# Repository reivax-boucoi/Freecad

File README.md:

### Freecad project repo
Here you'll find misc. 3D modeling projects ranging from home improvement to electronics tinkering.

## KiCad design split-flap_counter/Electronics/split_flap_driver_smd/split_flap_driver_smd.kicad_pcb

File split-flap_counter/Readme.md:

# Split flap counter project

This project started as a joke, to display the "number of consecutive days without incident", as we were blowing up chips regularly in the lab.

The counter consists of 2 digit wheels capable of displaying the numbers 00 through 99. (Given the frequency of incidents, a 3rd wheel wasn't considered).
Each day, the counter increments by 1. When a "happy little accident" occurs, simply insert a chip into the bin to cause the counter to reset in a satisfying motion.

This project was developped in a couple days, mixing 3D printing, electronics and minimal code.

## Hardware

### Mechanicals

The hardware was designed using Freecad 0.9 for the mechanical part. 
It uses multimaterial printing for the digit flaps, and regular PLA prints for the rest. The 2 wheels consist of mirrored parts facing each other, the assembly providing overall support of the drums.
The base structure was inspired by [Thomas H 3D](https://www.printables.com/model/69603-split-flap-counter-fully-printable) project, his being a single digit purely manual version. The flaps were customized for multi-material printing by [0Celta](https://www.printables.com/model/133058-multi-material-flaps-for-split-flap-counter).  

A ready made printable of the structure can be found [here](/Mechanical/3mF_exports_toPrint/full_plate.3mF).  
The individual printable parts are located in [/Mechanical/3mF_exports_toPrint/](/Mechanical/3mF_exports_toPrint/):
- 2x **Drum**
- 2x **Drum_end**
- 2x **Frame** (1 normal, 1 mirrored)
- 1x **JointKey**
- 1x **JointShaft**
- 2x **Flaps** (sets of 5 dual sided flaps)  

Additionnal hardware required:
- 2x **28-BYJ-48** 5V stepper motors
- 4x **M2x10** screws for the limit switches
- 4x **M3x8** screws for the motor mount
- 2x limit switches: mine were salvaged from an old industrial grade printer, I don't have the reference, they are similar-ish to Alps SSCTL10400.  

2 ventilation valve stepper motors are used, which are dirt cheap and run of 5V directly. They have a resolution of approx. 2048 steps per turn (in full step mode, not exact !) which is plenty for our application. One drawback is that they are quite slow: I found 5RPM to be a reliable value, i.e. ~12s to complete a revolution. Sliding lever microswitches provide zeroing on each wheel.  

### Assembly

### Electronics

Kicad 8.0 was used for the electronics (schematic and placement), although the circuit was manually assembled using dead-bug technique later on, because of it's simplicity. Nonetheless, a [schematic](/split-flap_counter/Electronics/split_flap_driver/schematic.pdf) and example [layout](/split-flap_counter/Electronics/split_flap_driver/) are available for reference.  

The project is powered by a 5V supply (>500mA required), which could be a generic USB wall charger.
The steppers are controlled using an ULN2003 Darlignton driver + an extra NPN since I required 8 channels for the 2x4 stepper coils. The buttons & limit switches inputs were filtered since the code is interrupt driven and without any debouncing. A hidden button allows manual incrementation for testing purposes.  

The 4MHz crystal oscillator frequency can be dialed-in using a trimmer cap to within tens of seconds per day of accuracy, which is sufficient for rough day keeping.

### Software

The software was developped in plain low level C and compiled using AVR-GCC and Avrdude (custom Makefile and [precompiled hex](/split-flap_counter/SW/main.hex) are provided). The MCU runs at 4MHz, and the program occupies 770 bytes of the 2kB of available program space.  

Fuse settings: `lfuse:w:0xfd:m -U hfuse:w:0xdf:m -U efuse:w:0xff:m`  

Resource allocation:
- TIMER0: triggers at ~400hz, used for stepper state machine and button debouncing.
- TIMER1: triggers every 8s, used for timekeeping (daily trigger)
- INT0: "zero" limit switch for the unit wheel. Configured as falling edge interrupt to reset position.
- INT1: "zero" limit switch for the tens wheel. Configured as falling edge interrupt to reset position.

The zeroing routine ensure a least half a turn of each wheel, even if the wheel was already diplaying a zero, for your enjoyment ☺.  
Upon zeroing, the time is also reset such that the display will increment 24 hours after the last reset.

To build the program use the `make` command, and use `make program` to upload it (be sure to specify your programmer in the Makefile *AVRDUDE_PROGRAMMER* field).

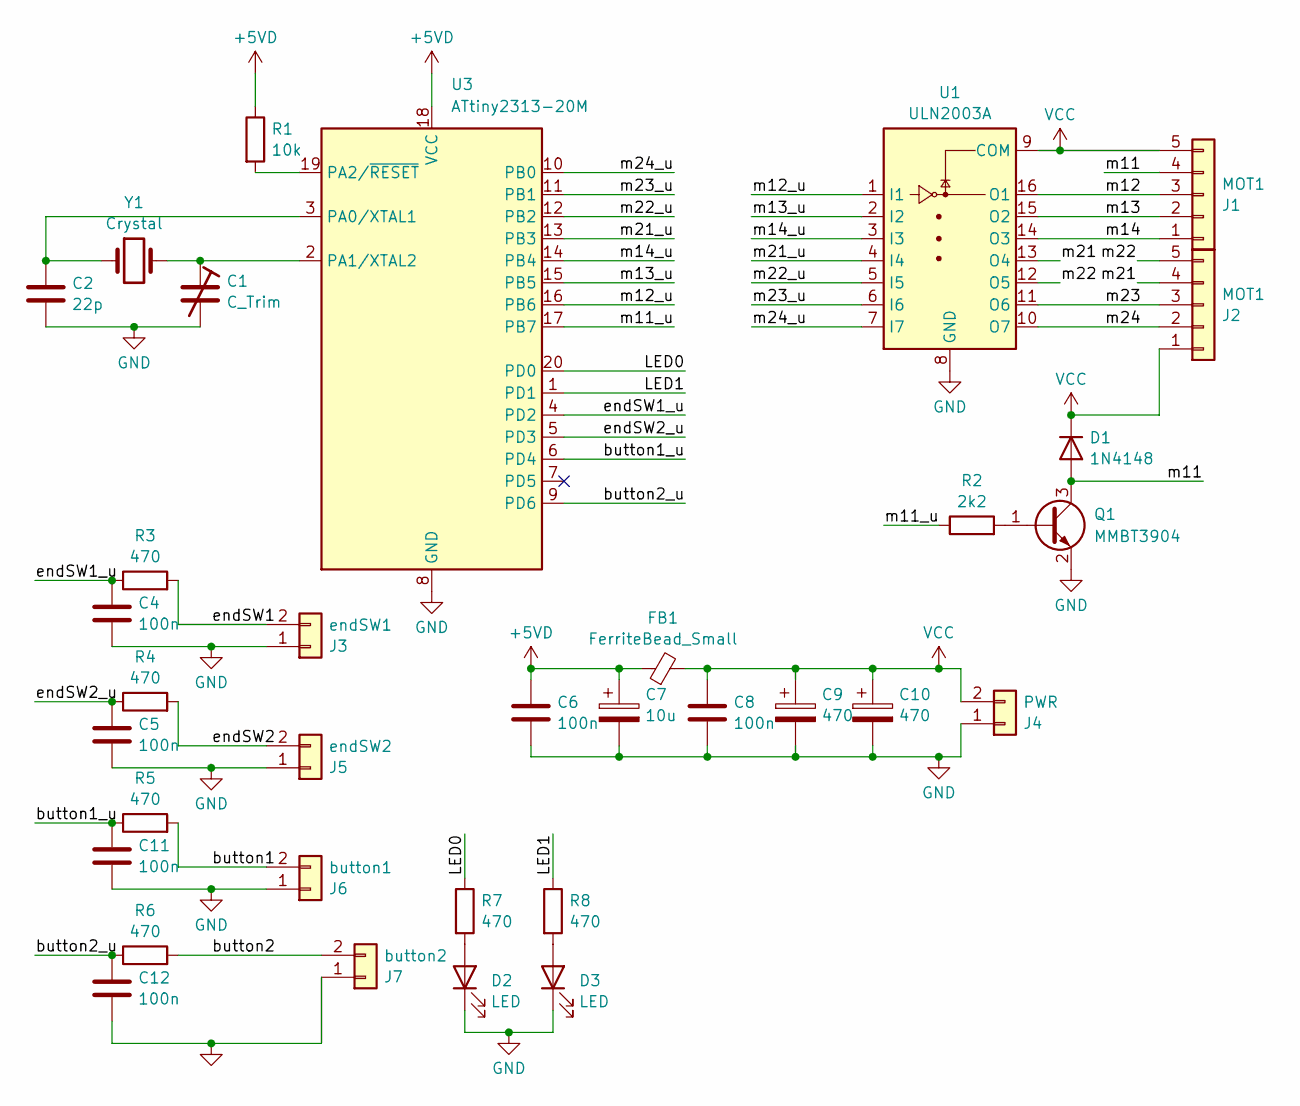
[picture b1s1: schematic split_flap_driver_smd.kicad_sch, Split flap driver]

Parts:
C1: C_Trim; Potentiometer_Bourns_3314J_Vertical
C2: 22p; C_0402_1005Metric
C4, C5, C6, C8, C11, C12: 100n; C_0402_1005Metric
C7: 10u; C_0805_2012Metric
C9, C10: 470; C_0805_2012Metric
D1: 1N4148; D_MicroMELF
D2, D3: LED; D_0603_1608Metric
FB1: FerriteBead_Small; L_0603_1608Metric
J1, J2: MOT1; JST_SH_SM05B-SRSS-TB_1x05-1MP_P1.00mm_Horizontal
J3: endSW1; JST_ZH_B2B-ZR_1x02_P1.50mm_Vertical
J4: PWR; JST_ZH_B2B-ZR_1x02_P1.50mm_Vertical
J5: endSW2; JST_ZH_B2B-ZR_1x02_P1.50mm_Vertical
J6: button1; JST_ZH_B2B-ZR_1x02_P1.50mm_Vertical
J7: button2; JST_ZH_B2B-ZR_1x02_P1.50mm_Vertical
Q1: MMBT3904; SOT-23
R1: 10k; R_0402_1005Metric
R2: 2k2; R_0402_1005Metric
R3, R4, R5, R6, R7, R8: 470; R_0402_1005Metric
U1: ULN2003A; TSSOP-16_4.4x5mm_P0.65mm
U3: ATtiny2313-20M; MLF-20-1EP_4x4mm_P0.5mm_EP2.6x2.6mm
Y1: Crystal; Crystal_SMD_2016-4Pin_2.0x1.6mm

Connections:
+5VD: C6.1, C7.1, FB1.1, R1.1, U3.18 (VCC)
/LED0: R7.1, U3.20 (PD0)
/LED1: R8.1, U3.1 (PD1)
/button1: J6.2, R5.2
/button1_u: C11.1, R5.1, U3.6 (PD4)
/button2: J7.2, R6.2
/button2_u: C12.1, R6.1, U3.9 (PD6)
/endSW1: J3.2, R3.2
/endSW1_u: C4.1, R3.1, U3.4 (PD2)
/endSW2: J5.2, R4.2
/endSW2_u: C5.1, R4.1, U3.5 (PD3)
/m11: D1.2 (A), J1.4, Q1.3 (C)
/m11_u: R2.1, U3.17 (PB7)
/m12: J1.3, U1.16 (O1)
/m12_u: U1.1 (I1), U3.16 (PB6)
/m13: J1.2, U1.15 (O2)
/m13_u: U1.2 (I2), U3.15 (PB5)
/m14: J1.1, U1.14 (O3)
/m14_u: U1.3 (I3), U3.14 (PB4)
/m21: J2.4, U1.13 (O4)
/m21_u: U1.4 (I4), U3.13 (PB3)
/m22: J2.5, U1.12 (O5)
/m22_u: U1.5 (I5), U3.12 (PB2)
/m23: J2.3, U1.11 (O6)
/m23_u: U1.6 (I6), U3.11 (PB1)
/m24: J2.2, U1.10 (O7)
/m24_u: U1.7 (I7), U3.10 (PB0)
GND: C1.2, C2.2, C4.2, C5.2, C6.2, C7.2, C8.2, C9.2, C10.2, C11.2, C12.2, D2.1 (K), D3.1 (K), J3.1, J4.1, J5.1, J6.1, J7.1, Q1.2 (E), U1.8 (GND), U3.8 (GND), U3.21 (GND)
unnamed: D2.2 (A), R7.2
unnamed: D3.2 (A), R8.2
unnamed: Q1.1 (B), R2.2
unnamed: C2.1, U3.3 (PA0/XTAL1), Y1.1
unnamed: C1.1, U3.2 (PA1/XTAL2), Y1.2
unnamed: R1.2, U3.19 (PA2/~RESET)
VCC: C8.1, C9.1, C10.1, D1.1 (K), FB1.2, J1.5, J2.1, J4.2, U1.9 (COM)

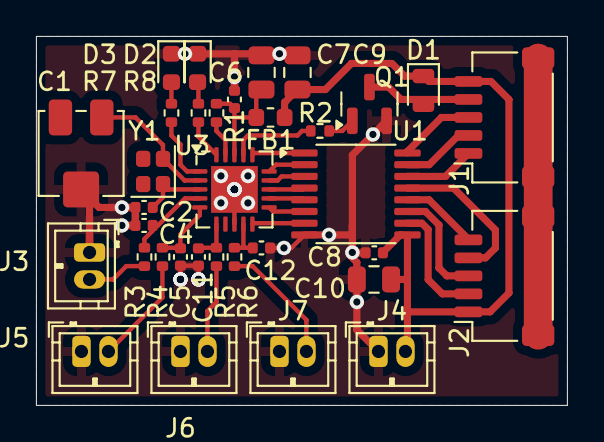
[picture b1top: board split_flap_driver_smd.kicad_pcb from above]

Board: 2 copper layers, 29.5 x 20.5 mm, 34 parts (0 on the bottom side), 35 nets.

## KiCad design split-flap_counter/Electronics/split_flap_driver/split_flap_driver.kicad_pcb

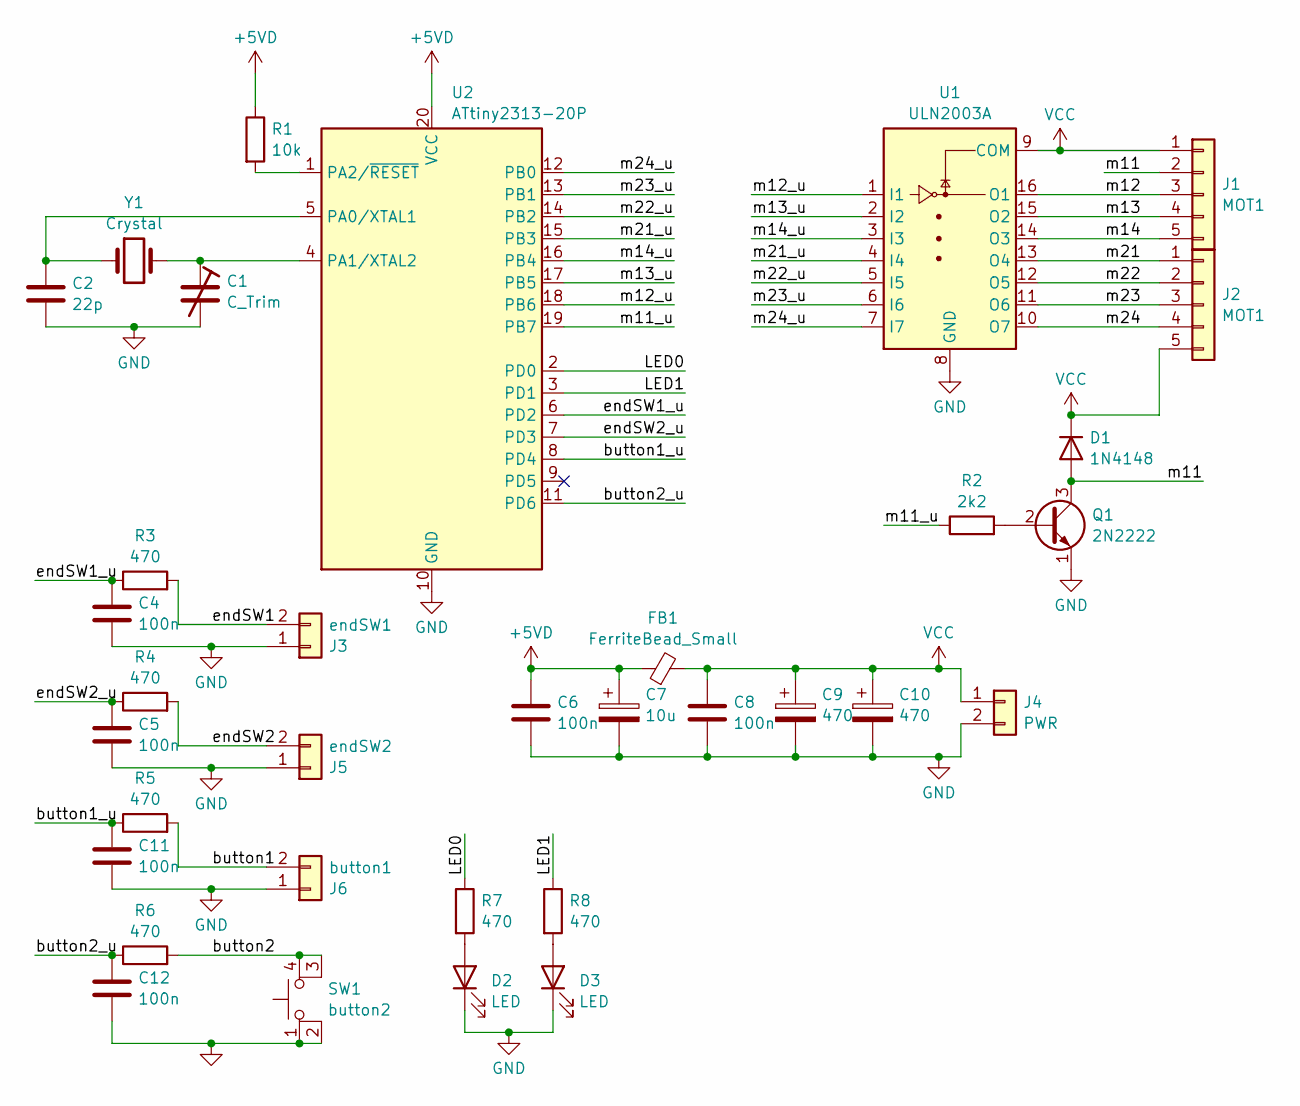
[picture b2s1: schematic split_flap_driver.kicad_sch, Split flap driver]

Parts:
C1: C_Trim; Potentiometer_Piher_PT-6-V_Vertical_Hole
C2: 22p; C_Disc_D5.0mm_W2.5mm_P5.00mm
C4, C5, C6, C8, C11, C12: 100n; C_Disc_D5.0mm_W2.5mm_P5.00mm
C7: 10u; CP_Radial_D6.3mm_P2.50mm
C9, C10: 470; CP_Radial_D10.0mm_P5.00mm
D1: 1N4148; D_DO-35_SOD27_P7.62mm_Horizontal
D2, D3: LED; LED_D5.0mm_Horizontal_O1.27mm_Z3.0mm
FB1: FerriteBead_Small; L_Axial_L5.3mm_D2.2mm_P7.62mm_Horizontal_Vishay_IM-1
J1, J2: MOT1; PinHeader_1x05_P2.54mm_Horizontal
J3: endSW1; PinHeader_1x02_P2.54mm_Horizontal
J4: PWR; TerminalBlock_bornier-2_P5.08mm
J5: endSW2; PinHeader_1x02_P2.54mm_Horizontal
J6: button1; PinHeader_1x02_P2.54mm_Horizontal
Q1: 2N2222; TO-92_Inline_Wide
R1: 10k; R_Axial_DIN0207_L6.3mm_D2.5mm_P7.62mm_Horizontal
R2: 2k2; R_Axial_DIN0207_L6.3mm_D2.5mm_P7.62mm_Horizontal
R3, R4, R5, R6, R7, R8: 470; R_Axial_DIN0207_L6.3mm_D2.5mm_P7.62mm_Horizontal
SW1: button2; SW_Push_2P1T_Toggle_CK_PVA1xxH4xxxxxxV2
U1: ULN2003A; DIP-16_W7.62mm_Socket_LongPads
U2: ATtiny2313-20P; DIP-20_W7.62mm
Y1: Crystal; Crystal_HC49-4H_Vertical

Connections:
+5VD: C6.1, C7.1, FB1.1, R1.1, U2.20 (VCC)
/LED0: R7.1, U2.2 (PD0)
/LED1: R8.1, U2.3 (PD1)
/button1: J6.2, R5.2
/button1_u: C11.1, R5.1, U2.8 (PD4)
/button2: R6.2, SW1.3 (K), SW1.4 (A)
/button2_u: C12.1, R6.1, U2.11 (PD6)
/endSW1: J3.2, R3.2
/endSW1_u: C4.1, R3.1, U2.6 (PD2)
/endSW2: J5.2, R4.2
/endSW2_u: C5.1, R4.1, U2.7 (PD3)
/m11: D1.2 (A), J1.2, Q1.3 (C)
/m11_u: R2.1, U2.19 (PB7)
/m12: J1.3, U1.16 (O1)
/m12_u: U1.1 (I1), U2.18 (PB6)
/m13: J1.4, U1.15 (O2)
/m13_u: U1.2 (I2), U2.17 (PB5)
/m14: J1.5, U1.14 (O3)
/m14_u: U1.3 (I3), U2.16 (PB4)
/m21: J2.1, U1.13 (O4)
/m21_u: U1.4 (I4), U2.15 (PB3)
/m22: J2.2, U1.12 (O5)
/m22_u: U1.5 (I5), U2.14 (PB2)
/m23: J2.3, U1.11 (O6)
/m23_u: U1.6 (I6), U2.13 (PB1)
/m24: J2.4, U1.10 (O7)
/m24_u: U1.7 (I7), U2.12 (PB0)
GND: C1.2, C2.2, C4.2, C5.2, C6.2, C7.2, C8.2, C9.2, C10.2, C11.2, C12.2, D2.1 (K), D3.1 (K), J3.1, J4.2, J5.1, J6.1, Q1.1 (E), SW1.1, SW1.2, U1.8 (GND), U2.10 (GND)
unnamed: D2.2 (A), R7.2
unnamed: D3.2 (A), R8.2
unnamed: Q1.2 (B), R2.2
unnamed: C2.1, U2.5 (PA0/XTAL1), Y1.1
unnamed: C1.1, U2.4 (PA1/XTAL2), Y1.2
unnamed: R1.2, U2.1 (PA2/~RESET)
VCC: C8.1, C9.1, C10.1, D1.1 (K), FB1.2, J1.1, J2.5, J4.1, U1.9 (COM)

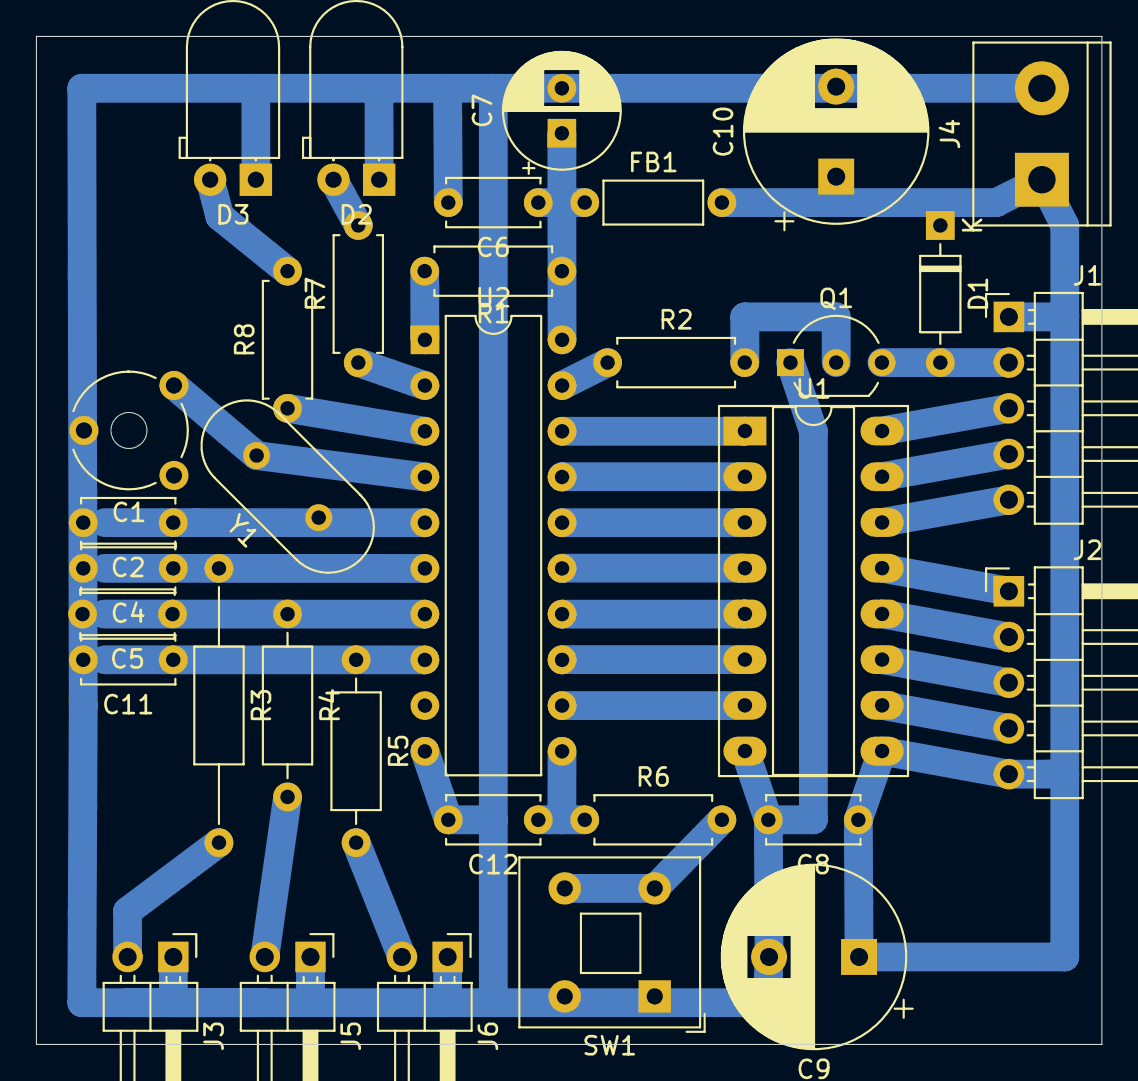
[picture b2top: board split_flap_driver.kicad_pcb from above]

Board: 2 copper layers, 59.2 x 56.0 mm, 34 parts (0 on the bottom side), 35 nets.

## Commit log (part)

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2025-07-30 Add MIT License
2025-07-30 added gitignore
2025-07-30 Remove .FCBak files and add to .gitignore
2025-07-30 added calmp coil
2025-08-04 added monitor Board
2025-08-04 added .gcode to .gitignore
2025-08-04 modified clamp, added banana model
2025-08-27 added source & starter fcstd
2025-08-27 added stepper
2025-08-27 added flaps
2025-08-27 added readme
2025-08-30 1st frame draft
2025-08-30 main complete
2025-08-30 added 3mf exports
2025-08-31 added SW folder
2025-08-31 main start
2025-08-31 added Electronics folder
2025-08-31 reorg Mechanical folder
2025-08-31 added mechanical pngs
2025-08-31 reorg mechanical pngs
2025-08-31 reorg mechanical 3mF
2025-08-31 Readme update
2025-08-31 added hex src
2025-09-01 -mFlaps as multimaterial
2025-09-02 program update
2025-09-12 -madded feets
2025-09-25 -madded SMD PCB version
2025-09-25 added SMD PCB version
2025-11-18 added garde boue
2025-11-18 up ad
2025-11-18 -madded new 3D
2026-01-26 added weather station start
2026-02-15 added AVRISP_enclosure
2026-02-15 added chamfers
2026-02-15 added faceplate svg+pdf
2026-02-16 modified Weather station case
2026-03-09 added improvedfront
2026-03-12 added ZG3766 model
